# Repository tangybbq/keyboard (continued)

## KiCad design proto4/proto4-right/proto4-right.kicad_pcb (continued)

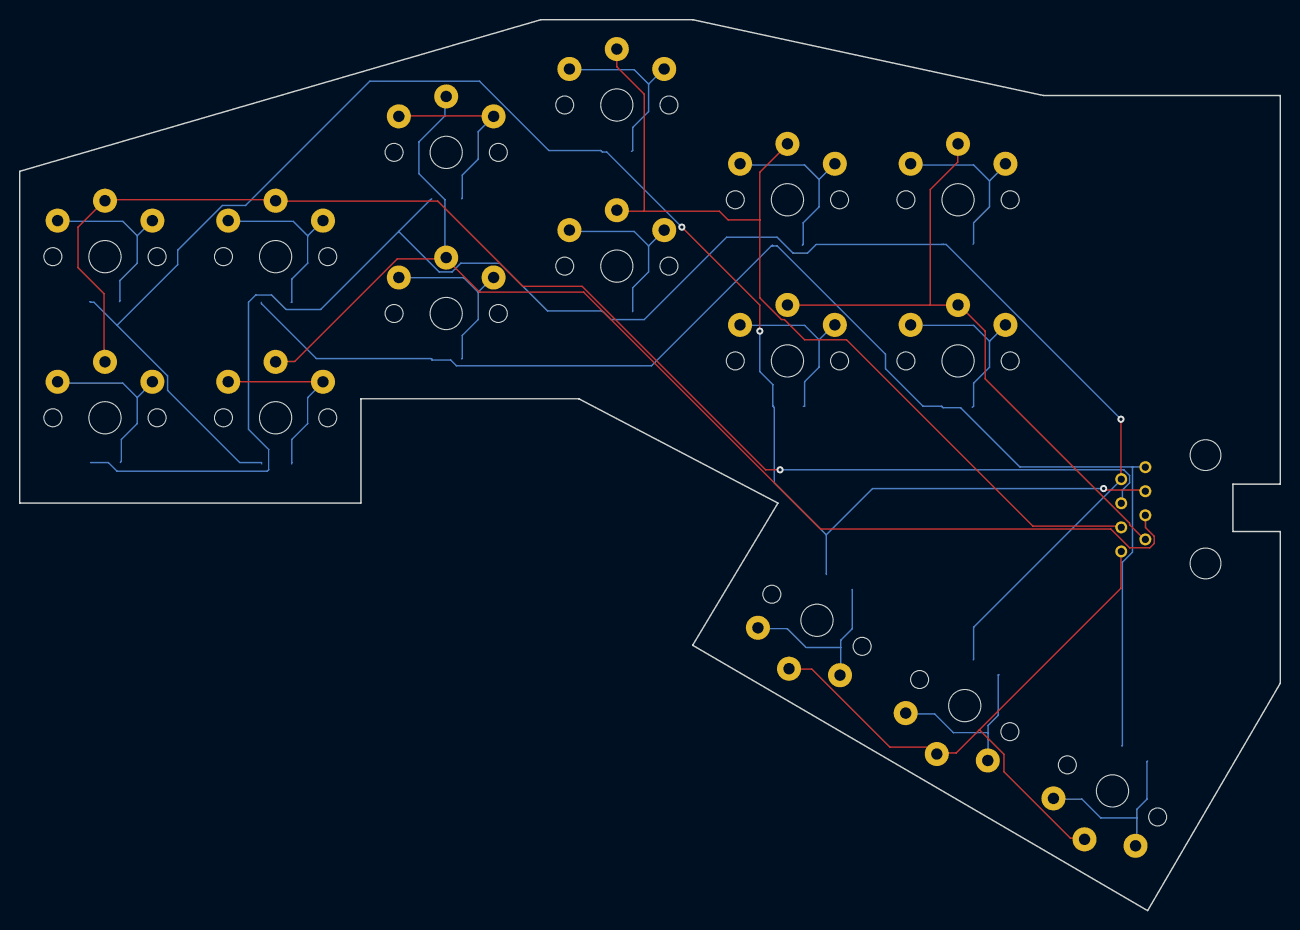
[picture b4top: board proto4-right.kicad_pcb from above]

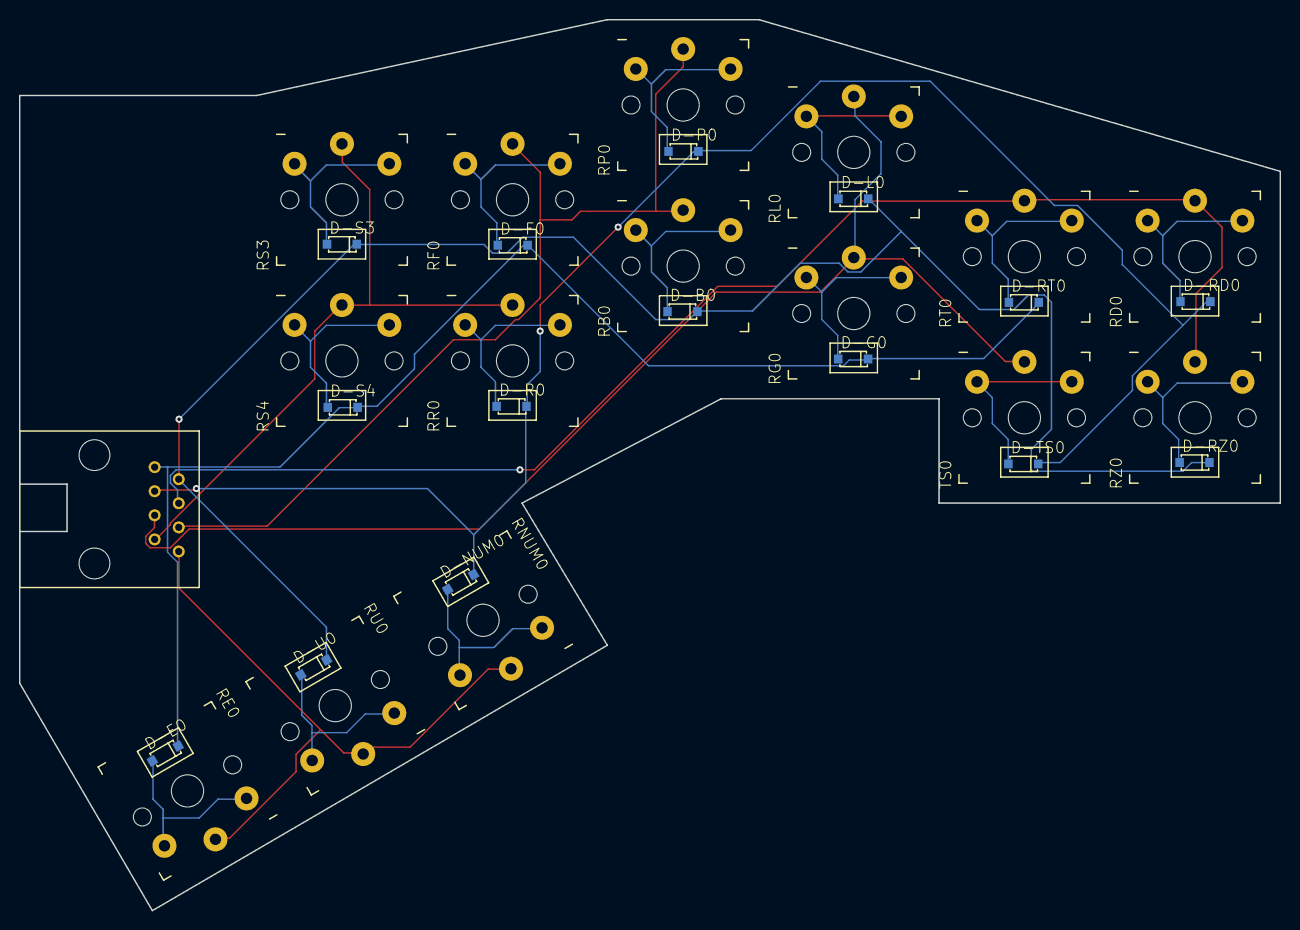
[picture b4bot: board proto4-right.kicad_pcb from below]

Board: 2 copper layers, 133.0 x 94.0 mm, 31 parts (31 on the bottom side), 23 nets.

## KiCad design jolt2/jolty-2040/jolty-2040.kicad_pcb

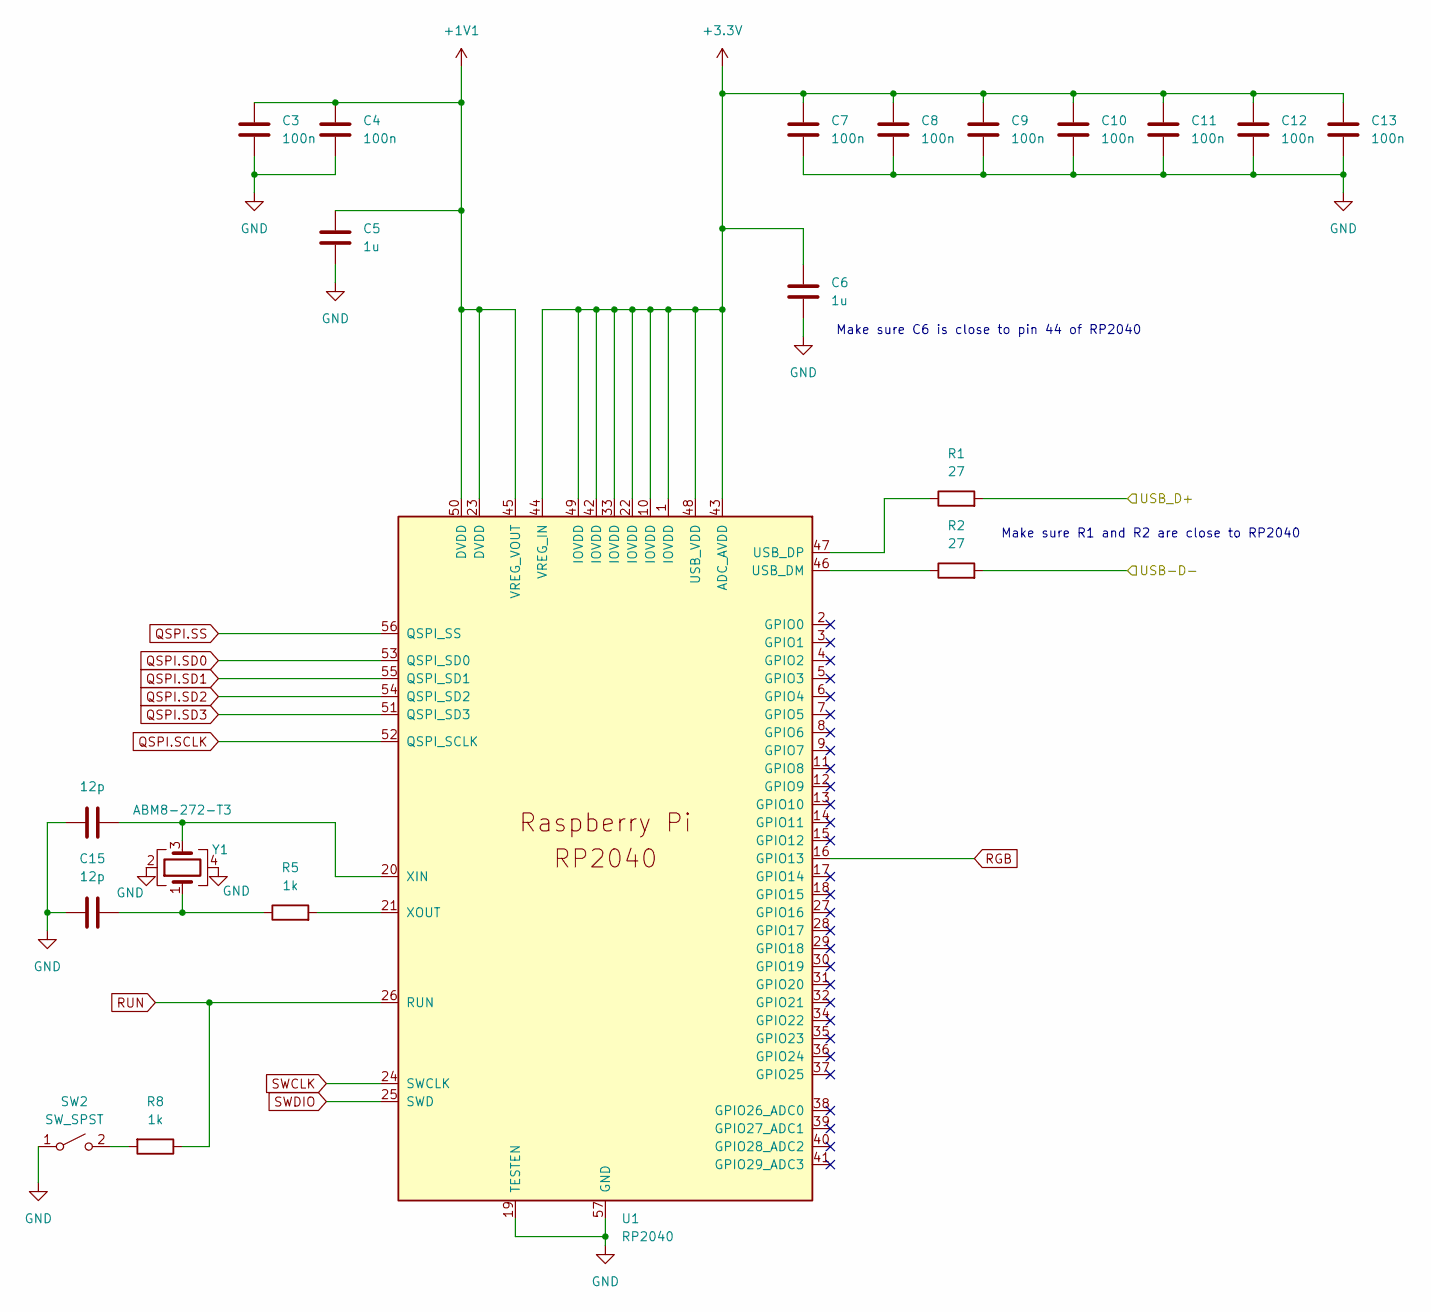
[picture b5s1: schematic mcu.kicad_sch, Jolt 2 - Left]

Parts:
C3, C4, C7, C8, C9, C10, C11, C12, C13: 100n; C_0402_1005Metric_Pad0.74x0.62mm_HandSolder
C5, C6: 1u; C_0402_1005Metric_Pad0.74x0.62mm_HandSolder
C14, C15: 12p; C_0402_1005Metric_Pad0.74x0.62mm_HandSolder
R1, R2: 27; R_0402_1005Metric_Pad0.72x0.64mm_HandSolder
R5, R8: 1k; R_0402_1005Metric_Pad0.72x0.64mm_HandSolder
SW2: SW_SPST; SW_Push_1P1T_NO_CK_KMR2
U1: RP2040; RP2040-QFN-56
Y1: ABM8-272-T3; Crystal_SMD_Abracon_ABM8G-4Pin_3.2x2.5mm

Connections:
+1V1: C3.1, C4.1, C5.1, U1.23 (DVDD), U1.45 (VREG_VOUT), U1.50 (DVDD)
+3.3V: C6.1, C7.1, C8.1, C9.1, C10.1, C11.1, C12.1, C13.1, U1.1 (IOVDD), U1.10 (IOVDD), U1.22 (IOVDD), U1.33 (IOVDD), U1.42 (IOVDD), U1.43 (ADC_AVDD), U1.44 (VREG_IN), U1.48 (USB_VDD), U1.49 (IOVDD); also elsewhere on the board
/USB_D+: R1.2; also elsewhere on the board
/USB_D-: R2.2; also elsewhere on the board
GND: C3.2, C4.2, C5.2, C6.2, C7.2, C8.2, C9.2, C10.2, C11.2, C12.2, C13.2, C14.1, C15.1, SW2.1 (A), U1.19 (TESTEN), U1.57 (GND), Y1.2, Y1.4; also elsewhere on the board
unnamed: C15.2, R5.1, Y1.1
unnamed: R8.2, SW2.2 (B)
unnamed: R2.1, U1.46 (USB_DM)
unnamed: R1.1, U1.47 (USB_DP)
unnamed: C14.2, U1.20 (XIN), Y1.3
unnamed: R5.2, U1.21 (XOUT)
QSPI.SCLK: U1.52 (QSPI_SCLK); also elsewhere on the board
QSPI.SD0: U1.53 (QSPI_SD0); also elsewhere on the board
QSPI.SD1: U1.55 (QSPI_SD1); also elsewhere on the board
QSPI.SD2: U1.54 (QSPI_SD2); also elsewhere on the board
QSPI.SD3: U1.51 (QSPI_SD3); also elsewhere on the board
QSPI.SS: U1.56 (QSPI_SS); also elsewhere on the board
RGB: U1.16 (GPIO13); also elsewhere on the board
RUN: R8.1, U1.26 (RUN); also elsewhere on the board
SWCLK: U1.24 (SWCLK); also elsewhere on the board
SWDIO: U1.25 (SWD); also elsewhere on the board

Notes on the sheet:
Make sure R1 and R2 are close to RP2040
Make sure C6 is close to pin 44 of RP2040

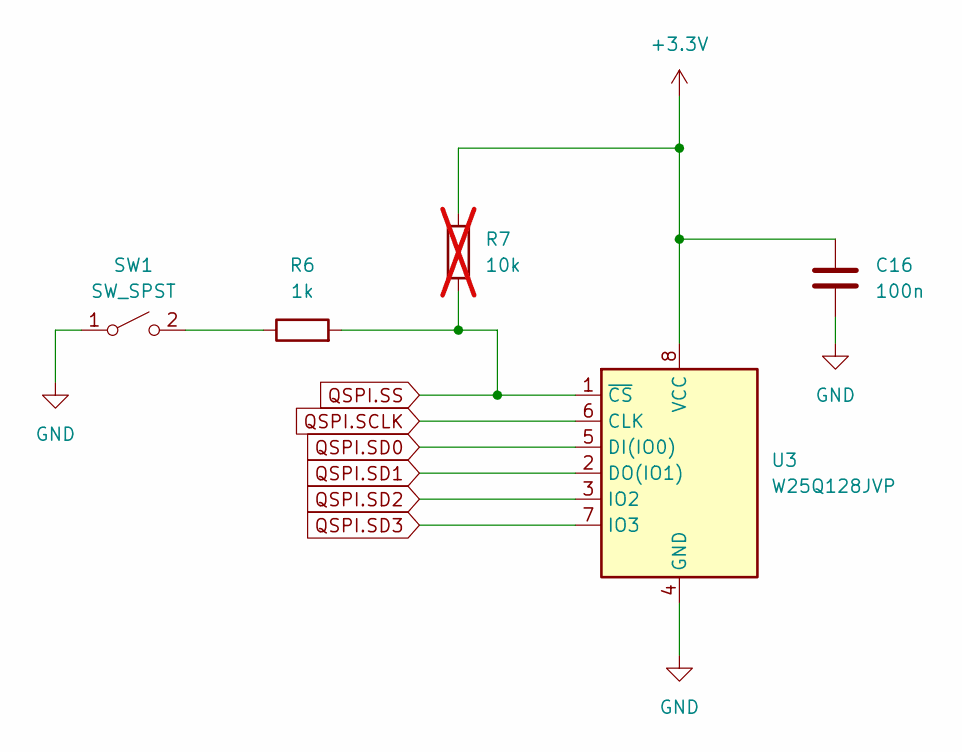
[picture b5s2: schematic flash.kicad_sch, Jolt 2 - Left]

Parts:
C16: 100n; C_0402_1005Metric_Pad0.74x0.62mm_HandSolder
R6: 1k; R_0402_1005Metric_Pad0.72x0.64mm_HandSolder
R7: 10k; R_0402_1005Metric_Pad0.72x0.64mm_HandSolder; not fitted
SW1: SW_SPST; SW_Push_1P1T_NO_CK_KMR2
U3: W25Q128JVP; WSON-8-1EP_6x5mm_P1.27mm_EP3.4x4.3mm

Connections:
+3.3V: C16.1, R7.2, U3.8 (VCC); also elsewhere on the board
GND: C16.2, SW1.1 (A), U3.4 (GND); also elsewhere on the board
unnamed: R6.1, SW1.2 (B)
QSPI.SCLK: U3.6 (CLK); also elsewhere on the board
QSPI.SD0: U3.5 (DI(IO0)); also elsewhere on the board
QSPI.SD1: U3.2 (DO(IO1)); also elsewhere on the board
QSPI.SD2: U3.3 (IO2); also elsewhere on the board
QSPI.SD3: U3.7 (IO3); also elsewhere on the board
QSPI.SS: R6.2, R7.1, U3.1 (~CS); also elsewhere on the board

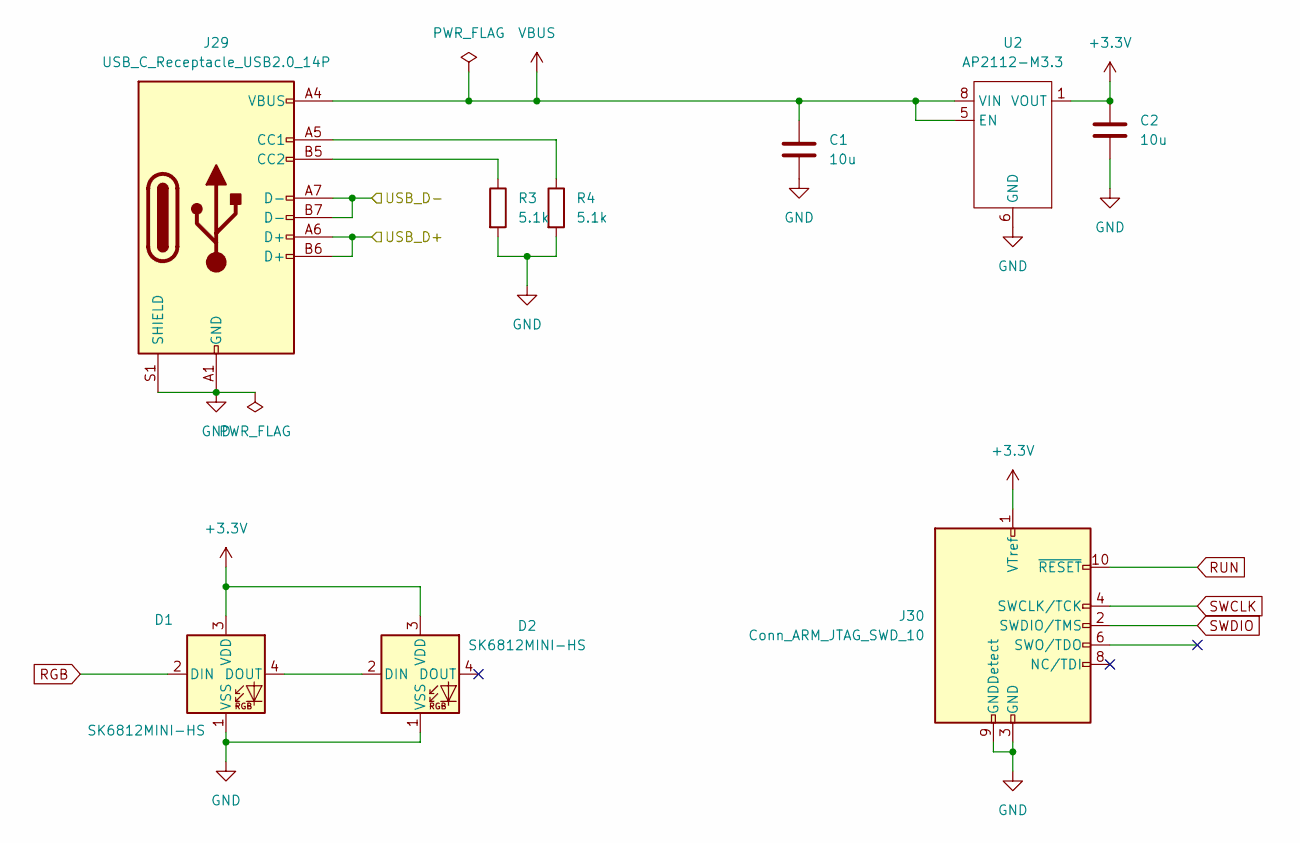
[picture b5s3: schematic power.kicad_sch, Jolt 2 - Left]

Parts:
C1, C2: 10u; C_0402_1005Metric_Pad0.74x0.62mm_HandSolder
D1, D2: SK6812MINI-HS; SK6812-MINI-HS
J29: USB_C_Receptacle_USB2.0_14P; USB_C_Receptacle_GCT_USB4085
J30: Conn_ARM_JTAG_SWD_10; Cortex-M-Debug10
R3, R4: 5.1k; R_0402_1005Metric_Pad0.72x0.64mm_HandSolder
U2: AP2112-M3.3; AP2112M-SO8

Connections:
+3.3V: C2.1, D1.3 (VDD), D2.3 (VDD), J30.1 (VTref), U2.1 (VOUT); also elsewhere on the board
/USB_D+: J29.A6 (D+), J29.B6 (D+); also elsewhere on the board
/USB_D-: J29.A7 (D-), J29.B7 (D-); also elsewhere on the board
GND: C1.2, C2.2, D1.1 (VSS), D2.1 (VSS), J29.A1 (GND), J29.A12 (GND), J29.B1 (GND), J29.B12 (GND), J29.S1 (SHIELD), J30.3 (GND), J30.5 (GND), J30.9 (GNDDetect), R3.2, R4.2, U2.6 (GND), U2.7 (GND); also elsewhere on the board
unnamed: D1.4 (DOUT), D2.2 (DIN)
unnamed: J29.A5 (CC1), R4.1
unnamed: J29.B5 (CC2), R3.1
RGB: D1.2 (DIN); also elsewhere on the board
RUN: J30.10 (~RESET); also elsewhere on the board
SWCLK: J30.4 (SWCLK/TCK); also elsewhere on the board
SWDIO: J30.2 (SWDIO/TMS); also elsewhere on the board
VBUS: C1.1, J29.A4 (VBUS), J29.A9 (VBUS), J29.B4 (VBUS), J29.B9 (VBUS), U2.5 (EN), U2.8 (VIN)

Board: 4 copper layers, 34 parts (0 on the bottom side), 26 nets, no tracks yet.

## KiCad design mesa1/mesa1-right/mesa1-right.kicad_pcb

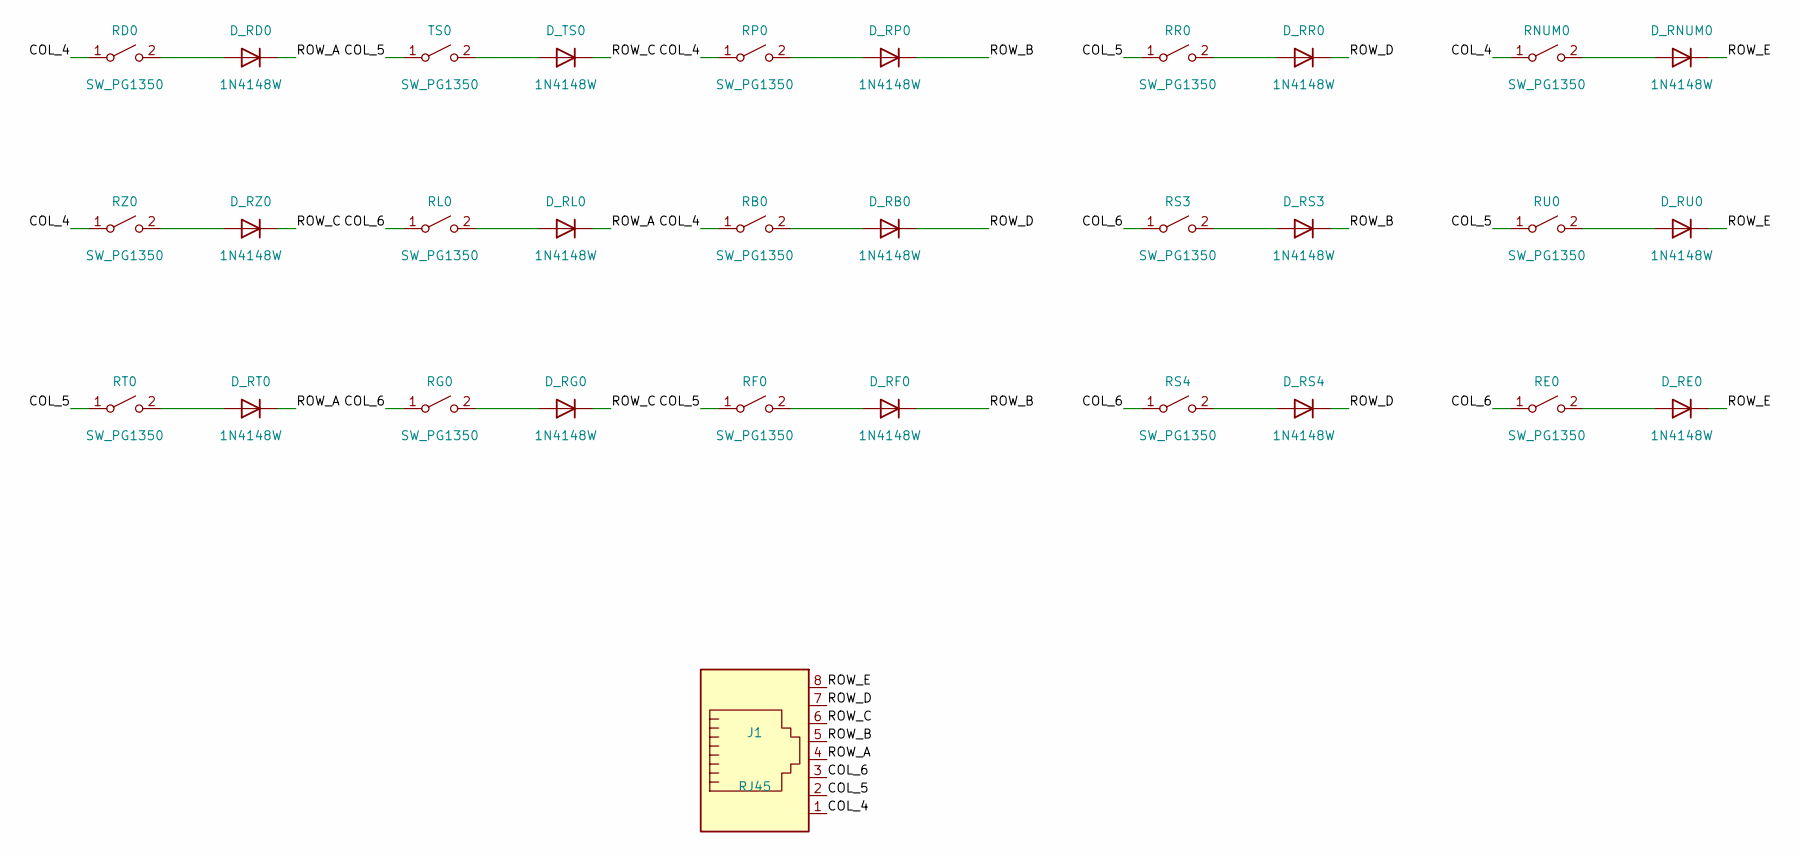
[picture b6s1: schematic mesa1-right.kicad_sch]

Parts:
D_RB0: 1N4148W; D_SOD-123
D_RD0: 1N4148W; D_SOD-123
D_RE0: 1N4148W; D_SOD-123
D_RF0: 1N4148W; D_SOD-123
D_RG0: 1N4148W; D_SOD-123
D_RL0: 1N4148W; D_SOD-123
D_RNUM0: 1N4148W; D_SOD-123
D_RP0: 1N4148W; D_SOD-123
D_RR0: 1N4148W; D_SOD-123
D_RS3, D_RS4: 1N4148W; D_SOD-123
D_RT0: 1N4148W; D_SOD-123
D_RU0: 1N4148W; D_SOD-123
D_RZ0: 1N4148W; D_SOD-123
D_TS0: 1N4148W; D_SOD-123
J1: RJ45; RJ45_Amphenol_54602-x08_Horizontal
RB0: SW_PG1350; Kailh_socket_PG1350
RD0: SW_PG1350; Kailh_socket_PG1350
RE0: SW_PG1350; Kailh_socket_PG1350
RF0: SW_PG1350; Kailh_socket_PG1350
RG0: SW_PG1350; Kailh_socket_PG1350
RL0: SW_PG1350; Kailh_socket_PG1350
RNUM0: SW_PG1350; Kailh_socket_PG1350
RP0: SW_PG1350; Kailh_socket_PG1350
RR0: SW_PG1350; Kailh_socket_PG1350
RS3, RS4: SW_PG1350; Kailh_socket_PG1350
RT0: SW_PG1350; Kailh_socket_PG1350
RU0: SW_PG1350; Kailh_socket_PG1350
RZ0: SW_PG1350; Kailh_socket_PG1350
TS0: SW_PG1350; Kailh_socket_PG1350

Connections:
/COL_4: J1.1, RB0.1 (A), RD0.1 (A), RNUM0.1 (A), RP0.1 (A), RZ0.1 (A)
/COL_5: J1.2, RF0.1 (A), RR0.1 (A), RT0.1 (A), RU0.1 (A), TS0.1 (A)
/COL_6: J1.3, RE0.1 (A), RG0.1 (A), RL0.1 (A), RS3.1 (A), RS4.1 (A)
/ROW_A: D_RD0.1 (K), D_RL0.1 (K), D_RT0.1 (K), J1.4
/ROW_B: D_RF0.1 (K), D_RP0.1 (K), D_RS3.1 (K), J1.5
/ROW_C: D_RG0.1 (K), D_RZ0.1 (K), D_TS0.1 (K), J1.6
/ROW_D: D_RB0.1 (K), D_RR0.1 (K), D_RS4.1 (K), J1.7
/ROW_E: D_RE0.1 (K), D_RNUM0.1 (K), D_RU0.1 (K), J1.8
unnamed: D_RB0.2 (A), RB0.2 (B)
unnamed: D_RD0.2 (A), RD0.2 (B)
unnamed: D_RE0.2 (A), RE0.2 (B)
unnamed: D_RF0.2 (A), RF0.2 (B)
unnamed: D_RG0.2 (A), RG0.2 (B)
unnamed: D_RL0.2 (A), RL0.2 (B)
unnamed: D_RNUM0.2 (A), RNUM0.2 (B)
unnamed: D_RP0.2 (A), RP0.2 (B)
unnamed: D_RR0.2 (A), RR0.2 (B)
unnamed: D_RS3.2 (A), RS3.2 (B)
unnamed: D_RS4.2 (A), RS4.2 (B)
unnamed: D_RT0.2 (A), RT0.2 (B)
unnamed: D_RU0.2 (A), RU0.2 (B)
unnamed: D_RZ0.2 (A), RZ0.2 (B)
unnamed: D_TS0.2 (A), TS0.2 (B)

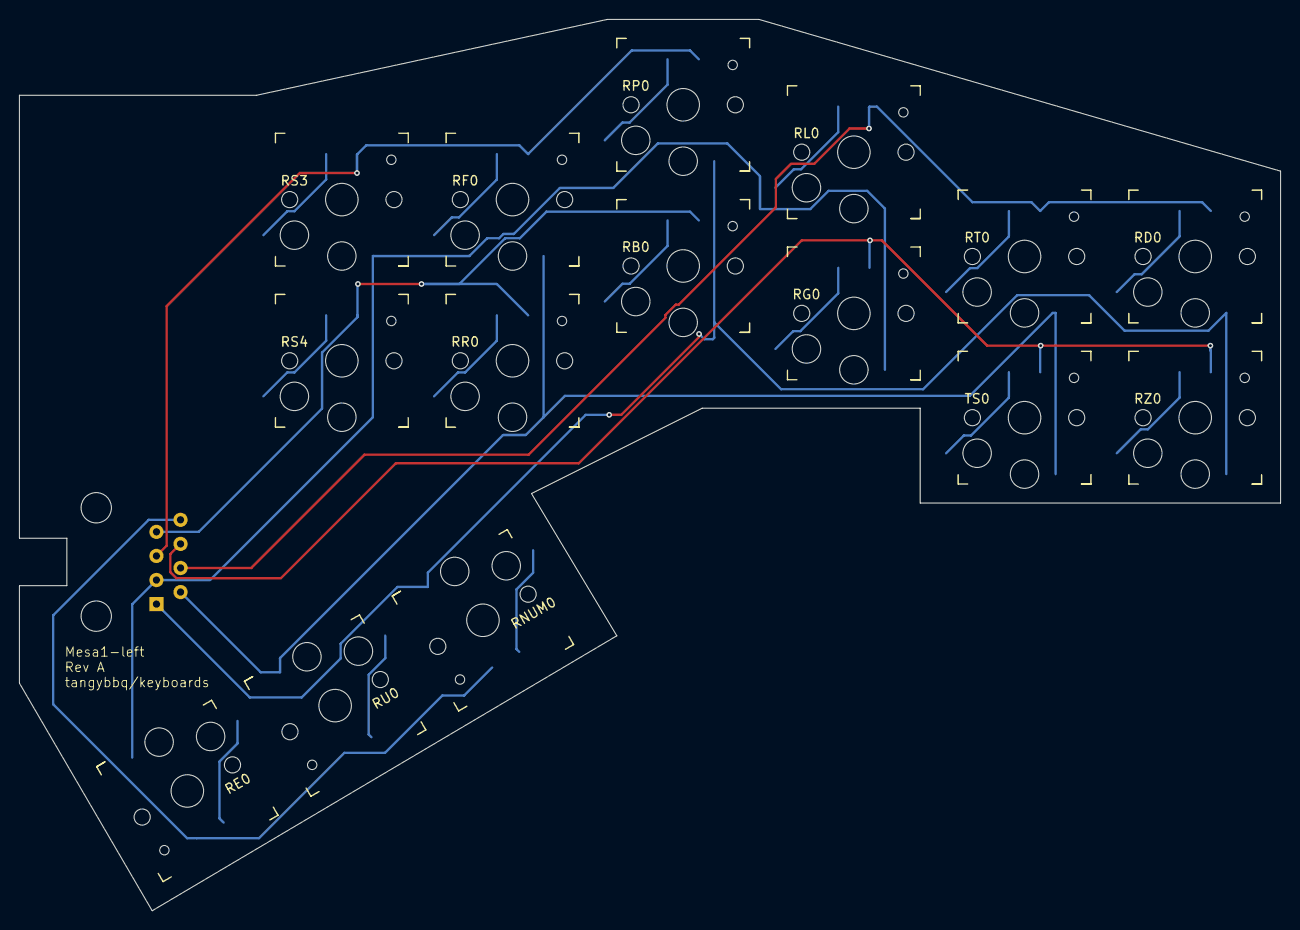
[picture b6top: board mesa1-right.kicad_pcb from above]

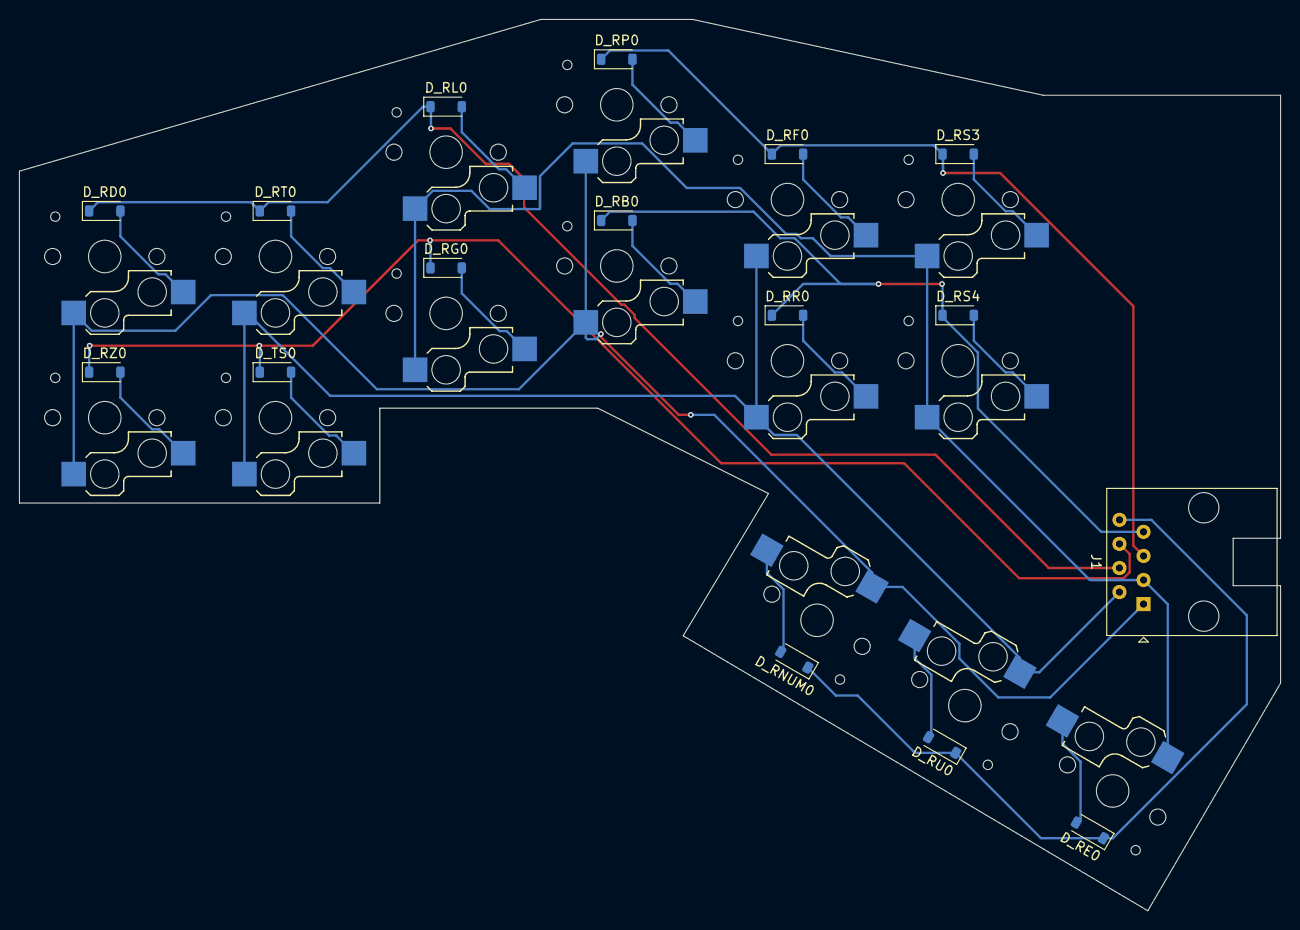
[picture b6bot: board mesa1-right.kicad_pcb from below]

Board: 2 copper layers, 133.0 x 94.0 mm, 31 parts (16 on the bottom side), 23 nets.

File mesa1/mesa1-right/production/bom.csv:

Designator,Footprint,Quantity,Value,LCSC Part #
"D_RB0, D_RD0, D_RE0, D_RF0, D_RG0, D_RL0, D_RNUM0, D_RP0, D_RR0, D_RS3, D_RS4, D_RT0, D_RU0, D_RZ0, D_TS0",D_SOD-123,15,1N4148W,
J1,RJ45_Amphenol_54602-x08_Horizontal,1,RJ45,
"RB0, RD0, RE0, RF0, RG0, RL0, RNUM0, RP0, RR0, RS3, RS4, RT0, RU0, RZ0, TS0",Kailh_socket_PG1350,15,SW_PG1350,

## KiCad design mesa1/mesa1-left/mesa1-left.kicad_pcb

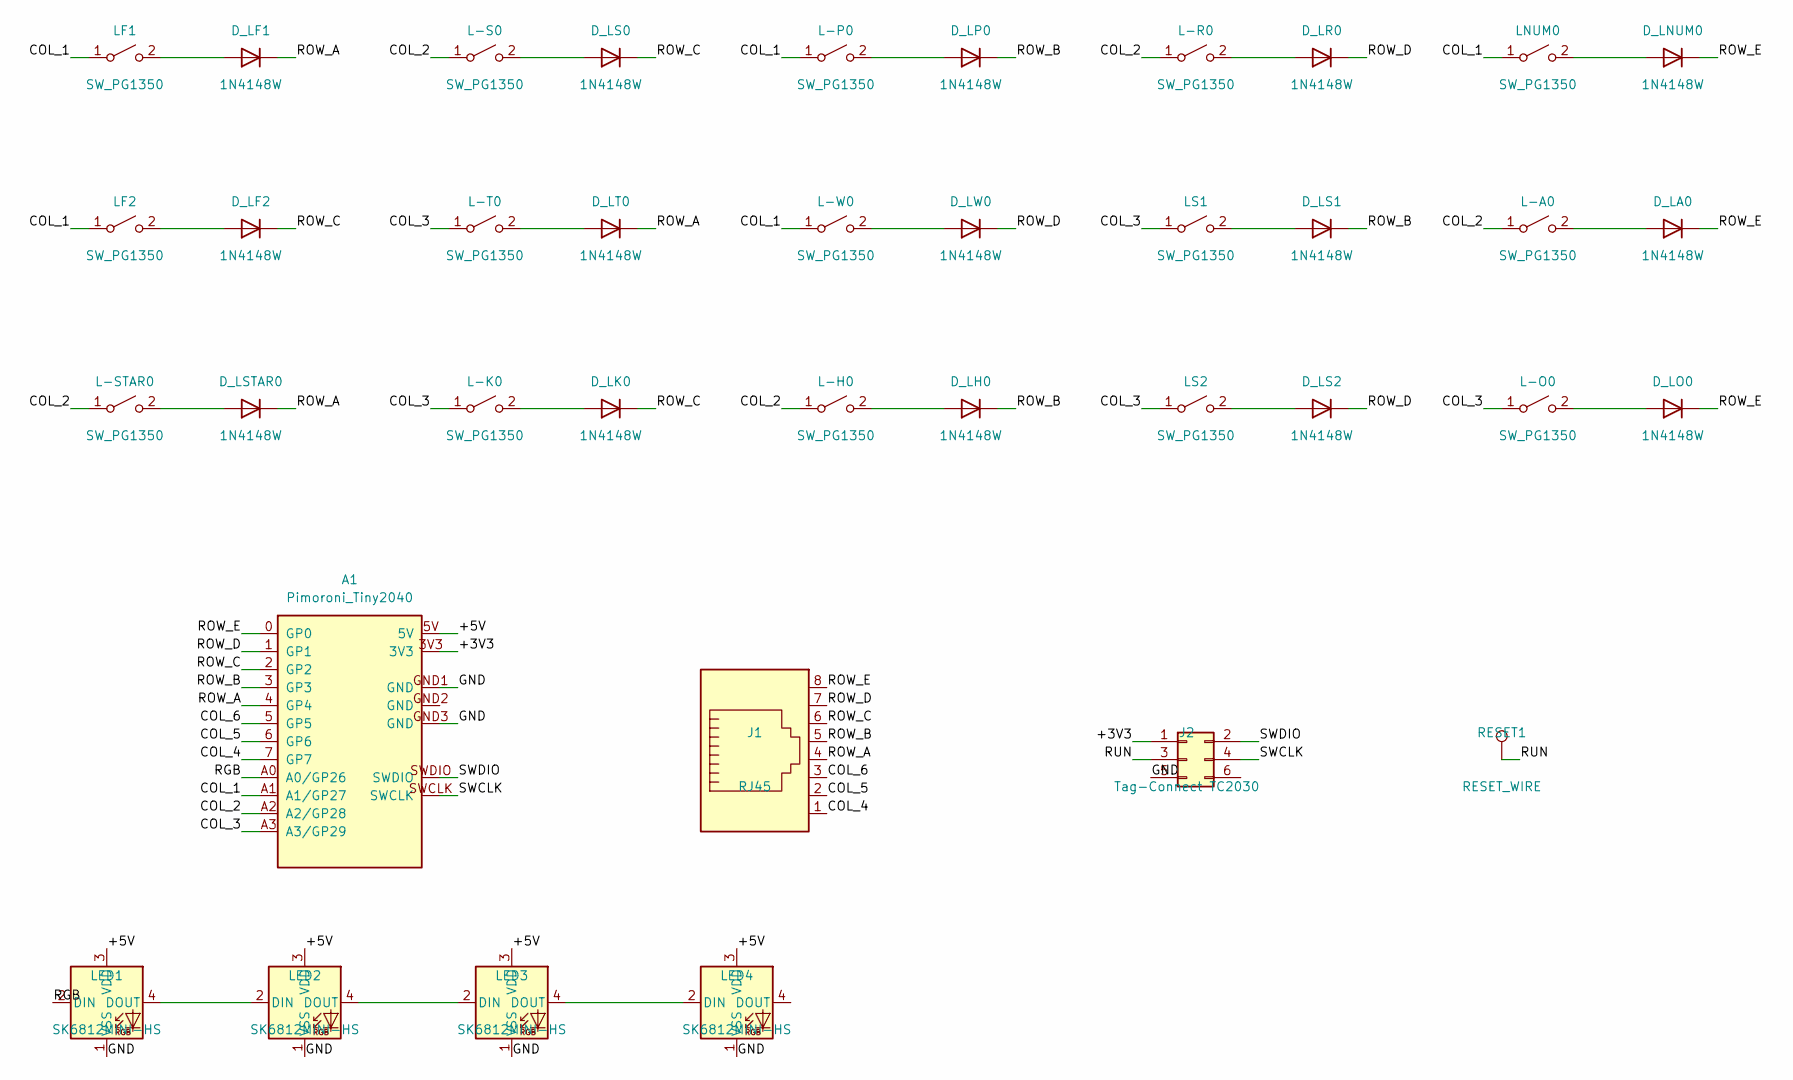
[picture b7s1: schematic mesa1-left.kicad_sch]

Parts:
A1: Pimoroni_Tiny2040
D_LA0: 1N4148W; D_SOD-123
D_LF1, D_LF2: 1N4148W; D_SOD-123
D_LH0: 1N4148W; D_SOD-123
D_LK0: 1N4148W; D_SOD-123
D_LNUM0: 1N4148W; D_SOD-123
D_LO0: 1N4148W; D_SOD-123
D_LP0: 1N4148W; D_SOD-123
D_LR0: 1N4148W; D_SOD-123
D_LS0, D_LS1, D_LS2: 1N4148W; D_SOD-123
D_LSTAR0: 1N4148W; D_SOD-123
D_LT0: 1N4148W; D_SOD-123
D_LW0: 1N4148W; D_SOD-123
J1: RJ45; RJ45_Amphenol_54602-x08_Horizontal
J2: Tag-Connect TC2030; Tag-Connect_TC2030-IDC-FP_2x03_P1.27mm_Vertical
L-A0: SW_PG1350; Kailh_socket_PG1350
L-H0: SW_PG1350; Kailh_socket_PG1350
L-K0: SW_PG1350; Kailh_socket_PG1350
L-O0: SW_PG1350; Kailh_socket_PG1350
L-P0: SW_PG1350; Kailh_socket_PG1350
L-R0: SW_PG1350; Kailh_socket_PG1350
L-S0: SW_PG1350; Kailh_socket_PG1350
L-STAR0: SW_PG1350; Kailh_socket_PG1350
L-T0: SW_PG1350; Kailh_socket_PG1350
L-W0: SW_PG1350; Kailh_socket_PG1350
LED1, LED2, LED3, LED4: SK6812MINI-HS; SK6812-MINI-HS
LF1, LF2: SW_PG1350; Kailh_socket_PG1350
LNUM0: SW_PG1350; Kailh_socket_PG1350
LS1, LS2: SW_PG1350; Kailh_socket_PG1350
RESET1: RESET_WIRE; TestPoint_Pad_2.0x2.0mm

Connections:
/+3V3: A1.3V3, J2.1
/+5V: A1.5V, LED1.3 (VDD), LED2.3 (VDD), LED3.3 (VDD), LED4.3 (VDD)
/COL_1: A1.A1 (A1/GP27), L-P0.1 (A), L-W0.1 (A), LF1.1 (A), LF2.1 (A), LNUM0.1 (A)
/COL_2: A1.A2 (A2/GP28), L-A0.1 (A), L-H0.1 (A), L-R0.1 (A), L-S0.1 (A), L-STAR0.1 (A)
/COL_3: A1.A3 (A3/GP29), L-K0.1 (A), L-O0.1 (A), L-T0.1 (A), LS1.1 (A), LS2.1 (A)
/COL_4: A1.7 (GP7), J1.1
/COL_5: A1.6 (GP6), J1.2
/COL_6: A1.5 (GP5), J1.3
/GND: A1.GND1 (GND), A1.GND3 (GND), J2.5, LED1.1 (VSS), LED2.1 (VSS), LED3.1 (VSS), LED4.1 (VSS)
/RGB: A1.A0 (A0/GP26), LED1.2 (DIN)
/ROW_A: A1.4 (GP4), D_LF1.1 (K), D_LSTAR0.1 (K), D_LT0.1 (K), J1.4
/ROW_B: A1.3 (GP3), D_LH0.1 (K), D_LP0.1 (K), D_LS1.1 (K), J1.5
/ROW_C: A1.2 (GP2), D_LF2.1 (K), D_LK0.1 (K), D_LS0.1 (K), J1.6
/ROW_D: A1.1 (GP1), D_LR0.1 (K), D_LS2.1 (K), D_LW0.1 (K), J1.7
/ROW_E: A1.0 (GP0), D_LA0.1 (K), D_LNUM0.1 (K), D_LO0.1 (K), J1.8
/RUN: J2.3, RESET1.1 (1_1)
/SWCLK: A1.SWCLK, J2.4
/SWDIO: A1.SWDIO, J2.2
unnamed: D_LA0.2 (A), L-A0.2 (B)
unnamed: D_LF1.2 (A), LF1.2 (B)
unnamed: D_LF2.2 (A), LF2.2 (B)
unnamed: D_LH0.2 (A), L-H0.2 (B)
unnamed: D_LK0.2 (A), L-K0.2 (B)
unnamed: D_LNUM0.2 (A), LNUM0.2 (B)
unnamed: D_LO0.2 (A), L-O0.2 (B)
unnamed: D_LP0.2 (A), L-P0.2 (B)
unnamed: D_LR0.2 (A), L-R0.2 (B)
unnamed: D_LS0.2 (A), L-S0.2 (B)
unnamed: D_LS1.2 (A), LS1.2 (B)
unnamed: D_LS2.2 (A), LS2.2 (B)
unnamed: D_LSTAR0.2 (A), L-STAR0.2 (B)
unnamed: D_LT0.2 (A), L-T0.2 (B)
unnamed: D_LW0.2 (A), L-W0.2 (B)
unnamed: LED1.4 (DOUT), LED2.2 (DIN)
unnamed: LED2.4 (DOUT), LED3.2 (DIN)
unnamed: LED3.4 (DOUT), LED4.2 (DIN)

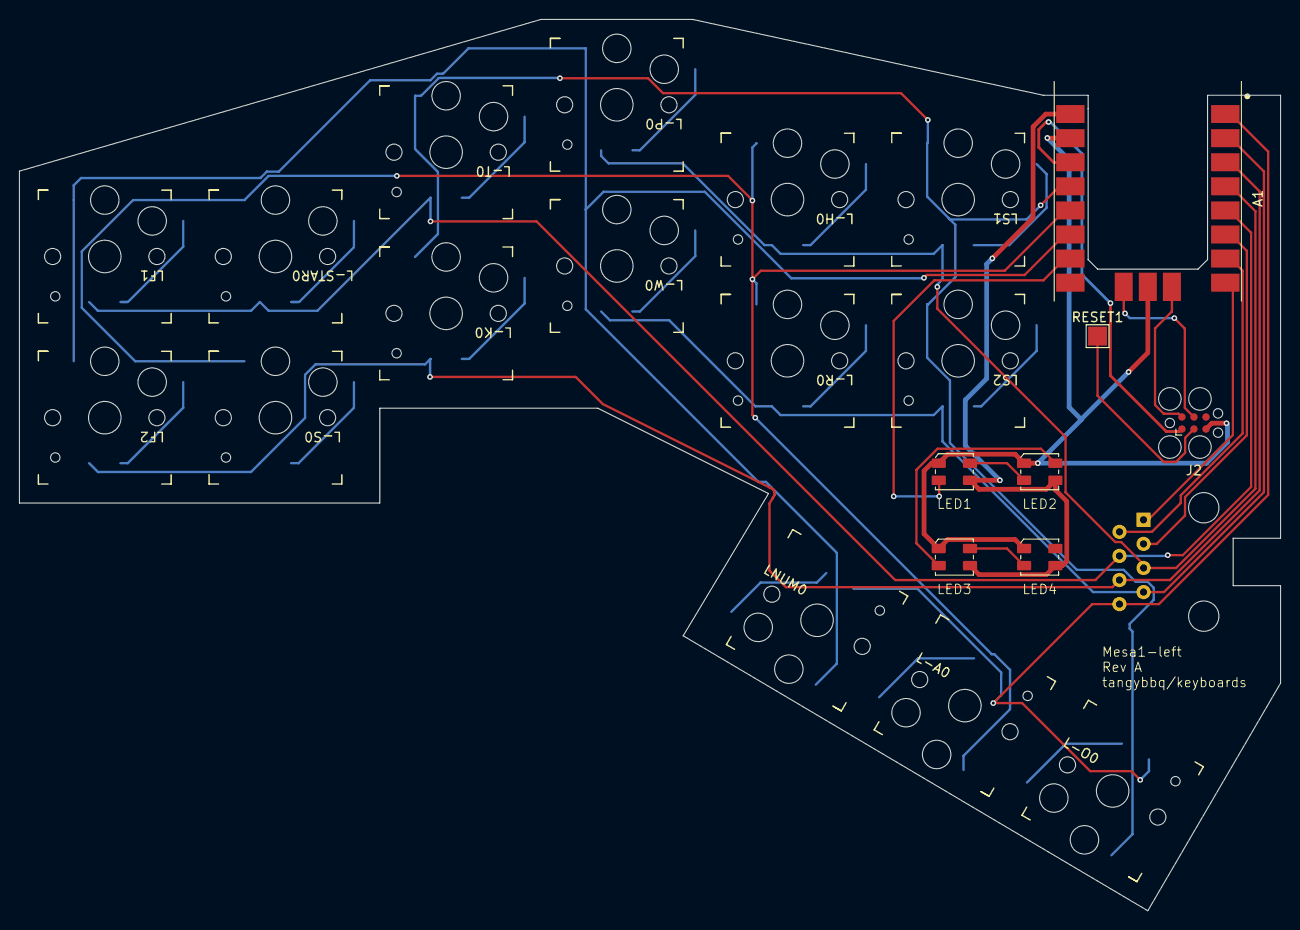
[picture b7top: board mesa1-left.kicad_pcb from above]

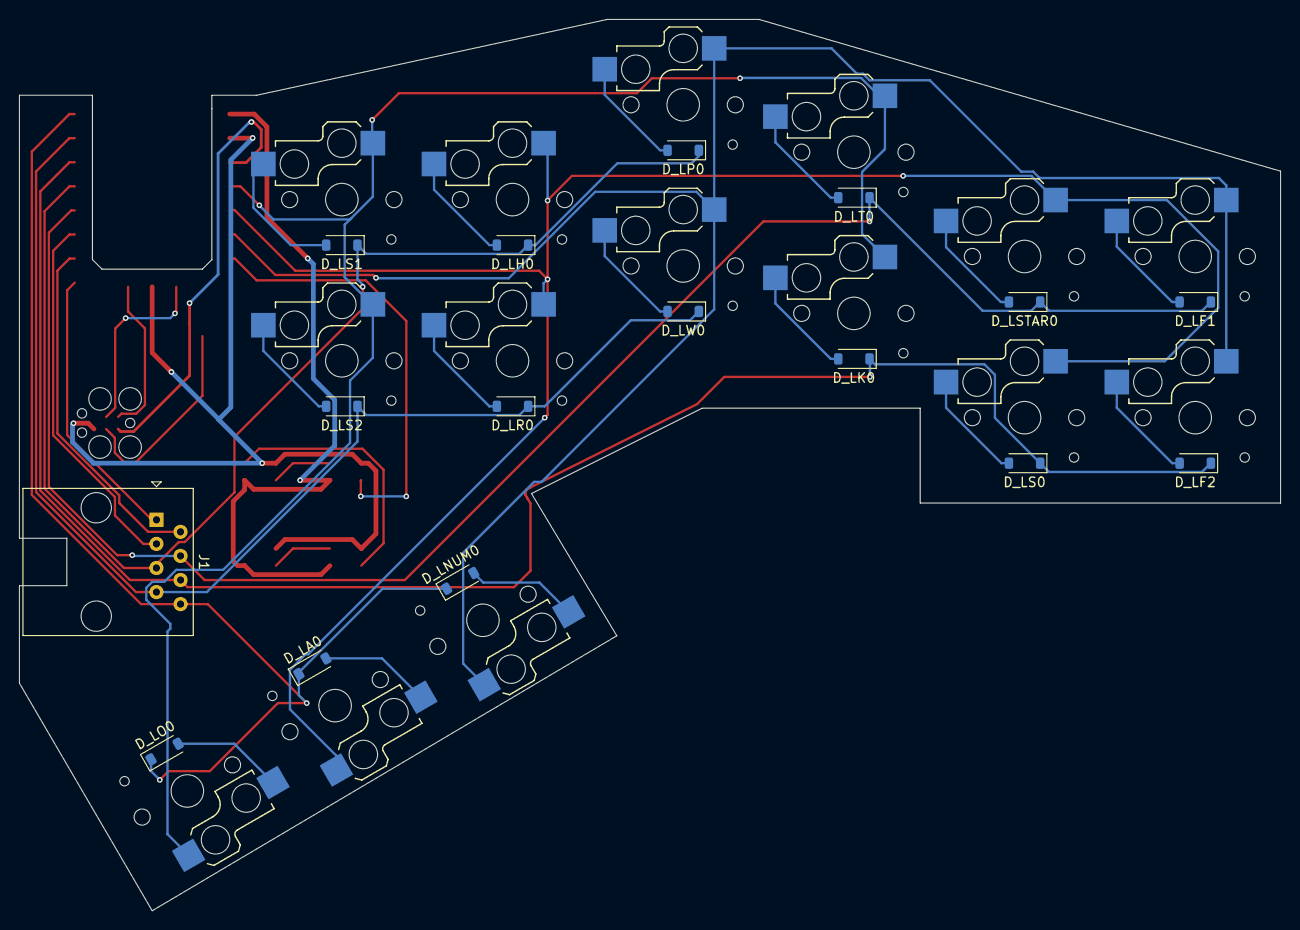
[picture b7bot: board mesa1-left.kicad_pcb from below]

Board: 2 copper layers, 133.0 x 94.0 mm, 38 parts (16 on the bottom side), 36 nets.
